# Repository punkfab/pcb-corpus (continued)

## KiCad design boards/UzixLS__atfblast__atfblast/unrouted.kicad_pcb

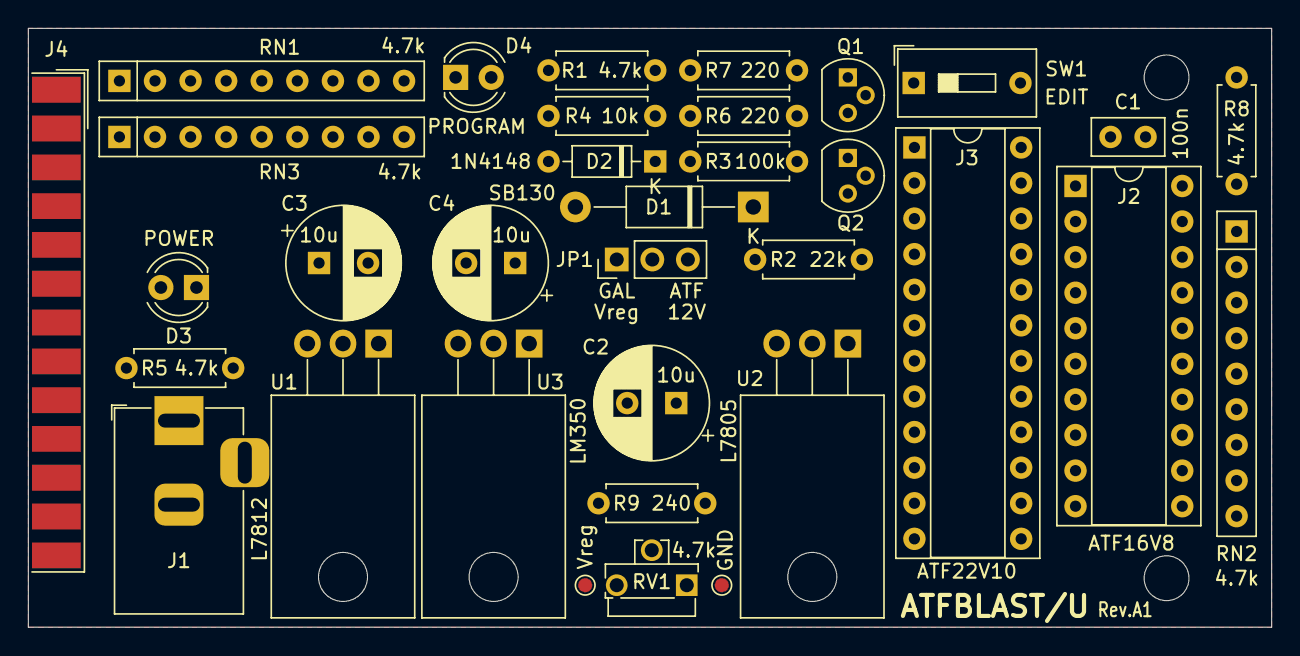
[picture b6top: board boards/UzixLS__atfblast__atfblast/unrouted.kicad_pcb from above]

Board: 2 copper layers, 88.8 x 42.8 mm, 36 parts (0 on the bottom side), 37 nets, no tracks yet.

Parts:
C1: 100n; C_Disc_D5.0mm_W2.5mm_P2.50mm
C2, C3, C4: 10u; CP_Radial_D8.0mm_P3.50mm
D1: SB130; D_DO-41_SOD81_P12.70mm_Horizontal
D2: 1N4148; D_DO-35_SOD27_P7.62mm_Horizontal
D3, D4: LED; LED_D4.0mm
H1, H2: MountingHole; MountingHole_3.2mm_M3
J1: DS-210; BarrelJack_Horizontal
J2: DIP20-panel; DIP-20_W7.62mm_Socket
J3: DIP24-panel; DIP-24_W7.62mm_Socket
J4: DB25_Male; DSUB-25_Male_EdgeMount_P2.77mm
JP1: Jumper_3; PinHeader_1x03_P2.54mm_Vertical
Q1: BC547; TO-92
Q2: BC557; TO-92
R1, R5, R8: 4.7k; R_Axial_DIN0207_L6.3mm_D2.5mm_P7.62mm_Horizontal
R2: 22k; R_Axial_DIN0207_L6.3mm_D2.5mm_P7.62mm_Horizontal
R3: 100k; R_Axial_DIN0207_L6.3mm_D2.5mm_P7.62mm_Horizontal
R4: 10k; R_Axial_DIN0207_L6.3mm_D2.5mm_P7.62mm_Horizontal
R6, R7: 220; R_Axial_DIN0207_L6.3mm_D2.5mm_P7.62mm_Horizontal
R9: 240; R_Axial_DIN0207_L6.3mm_D2.5mm_P7.62mm_Horizontal
RN1, RN2, RN3: 4.7k; R_Array_SIP9
RV1: 4.7k; Potentiometer_Runtron_RM-063_Horizontal
SW1: SW_DIP_x01; SW_DIP_SPSTx01_Slide_9.78x4.72mm_W7.62mm_P2.54mm
TP1: Vreg; TestPoint_Pad_D1.0mm
TP2: GND; TestPoint_Pad_D1.0mm
U1: L7812; TO-220-3_Horizontal_TabDown
U2: L7805; TO-220-3_Horizontal_TabDown
U3: LM350; TO-220-3_Horizontal_TabDown

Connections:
+5V: C1.1, C2.1, D2.2 (A), J2.20, J3.24, R5.1, RN1.1 (common), RN3.1 (common), U2.3 (OUT)
+12V: C3.1, D1.2 (A), JP1.3 (B), U1.3 (OUT), U2.1 (IN)
/ACK: J2.12, J3.14, J4.10, RN3.6 (R5)
/AUTO: J4.14, R4.2
/D0: J2.9, J3.11, J4.2, RN1.3 (R2)
/D1: J4.3, R6.2, RN1.4 (R3)
/D2: J2.3, J3.5, J4.4, RN1.5 (R4)
/D3: J2.4, J3.6, J4.5, RN1.7 (R6)
/D4: J2.5, J3.7, J4.6, RN3.2 (R1)
/D5: J2.6, J3.8, J4.7, RN3.3 (R2)
/D6: J2.7, J3.9, J4.8, RN3.4 (R3)
/D7: J2.8, J3.10, J4.9, RN3.5 (R4)
/EDIT: D2.1 (K), J2.2, J3.2, SW1.2
/P_V-: J2.19, J3.3, R7.1
/RA0: J2.18, J3.4, R6.1
/SELECT: J4.17, R7.2, RN1.6 (R5)
/STROBE: J2.11, J3.13, J4.1, RN1.2 (R1)
GND: C1.2, C2.2, C3.2, C4.2, D3.1 (K), J1.2, J1.3, J2.1, J2.10, J3.1, J3.12, J4.18, J4.19, J4.20, J4.21, J4.22, J4.23, J4.24, Q1.3 (E), R8.2, RN2.1 (common), RV1.2, TP2.1, U1.2 (GND), U2.2 (GND)
unnamed: C4.1, JP1.1 (A), R9.1, TP1.1, U3.2 (VO)
unnamed: D1.1 (K), Q2.3 (C), SW1.1
unnamed: D3.2 (A), R5.2
unnamed: D4.1 (K), Q1.1 (C), R3.1
unnamed: D4.2 (A), R1.2
unnamed: J1.1, U1.1 (IN), U3.3 (VI)
unnamed: J2.13, J3.15, RN2.9 (R8)
unnamed: J2.14, J3.16, RN2.8 (R7)
unnamed: J2.15, J3.17, RN2.7 (R6)
unnamed: J2.16, J3.18, RN2.6 (R5)
unnamed: J2.17, J3.19, RN2.5 (R4)
unnamed: J3.20, RN2.4 (R3)
unnamed: J3.21, RN2.3 (R2)
unnamed: J3.22, RN2.2 (R1)
unnamed: J3.23, R8.1
unnamed: JP1.2 (C), Q2.1 (E), R1.1, R2.2
unnamed: Q1.2 (B), R4.1
unnamed: Q2.2 (B), R2.1, R3.2
unnamed: R9.2, RV1.3, U3.1 (ADJ)

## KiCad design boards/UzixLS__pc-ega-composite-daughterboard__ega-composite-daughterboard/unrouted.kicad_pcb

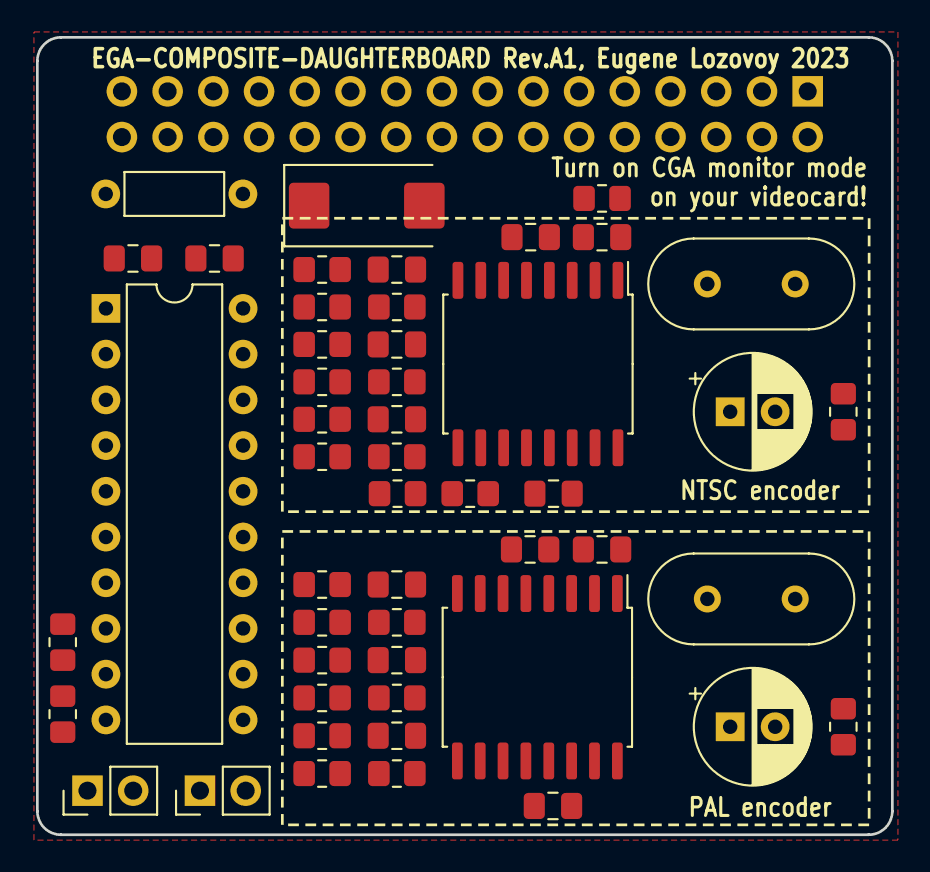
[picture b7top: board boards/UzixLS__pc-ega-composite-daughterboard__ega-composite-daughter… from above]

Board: 2 copper layers, 47.5 x 44.3 mm, 51 parts (1 on the bottom side), 43 nets, no tracks yet.

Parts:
C1, C2, C3, C6, C7, C8: 100n; C_0805_2012Metric_Pad1.18x1.45mm_HandSolder
C4, C9: 220u; CP_Radial_D6.3mm_P2.50mm
C5, C10: 4.3p; C_0805_2012Metric_Pad1.18x1.45mm_HandSolder
C11: 220u/10V; CP_EIA-7343-31_Kemet-D_Pad2.25x2.55mm_HandSolder
C12, C13, C14, C15, C16, C17: 1u; C_0805_2012Metric_Pad1.18x1.45mm_HandSolder
FB1: FB_Lossy; L_Axial_L5.3mm_D2.2mm_P7.62mm_Horizontal_Vishay_IM-1
J1: EGA Feature Connector; PinHeader_2x16_P2.54mm_Vertical
JP1, JP2: Jumper_2_Open; PinHeader_1x02_P2.54mm_Vertical
R1, R3, R5, R13, R15, R17: 390; R_0805_2012Metric_Pad1.20x1.40mm_HandSolder
R2, R4, R6, R14, R16, R18: 680; R_0805_2012Metric_Pad1.20x1.40mm_HandSolder
R7, R8, R9, R10, R19, R20, R21, R22: 75; R_0805_2012Metric_Pad1.20x1.40mm_HandSolder
R11, R12: 10k; R_0805_2012Metric_Pad1.20x1.40mm_HandSolder
R23, R24, R25: 0; R_0805_2012Metric_Pad1.20x1.40mm_HandSolder
U1, U3: AD724; SOIC-16W_7.5x10.3mm_P1.27mm
U2: ATF16V8; DIP-20_W7.62mm
Y1: 3.579545 MHz; Crystal_HC49-4H_Vertical
Y2: 4.433619 MHz; Crystal_HC49-4H_Vertical

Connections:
+5V: C13.2, FB1.1, J1.32
+5VA: C11.1, C12.2, C14.2, C15.2, C16.2, C17.2, FB1.2, R11.1, R12.1, R24.2, U1.1 (STDN), U1.4 (AVCC), U1.5 (ENCD), U1.14 (DVCC), U2.20 (VCC), U3.4 (AVCC), U3.5 (ENCD), U3.14 (DVCC)
/14M: J1.26, R23.2
/B0: R6.1, R18.1, U2.19 (IO1)
/B0_IN: J1.23, U2.6 (I6)
/B1: R5.1, R17.1, U2.18 (IO2)
/B1_IN: J1.14, U2.3 (I3)
/G0: R4.1, R16.1, U2.17 (I03)
/G0_IN: J1.22, U2.8 (I8)
/G1: R3.1, R15.1, U2.16 (IO4)
/G1_IN: J1.12, U2.4 (I4)
/HIN: J1.24, U2.7 (I7)
/HSYNC: U1.16 (HSYNC), U2.12 (IO8), U3.16 (HSYNC)
/NTSC: J1.4, R7.1
/PAL: J1.5, R19.1
/R0: R2.1, R14.1, U2.15 (IO5)
/R0_IN: J1.13, U2.2 (I2)
/R1: R1.1, R13.1, U2.14 (IO6)
/R1_IN: J1.15, U2.1 (I1/CLK)
/VIN: J1.25, U2.5 (I5)
/VSYNC: U1.15 (VSYNC), U2.13 (IO7), U3.15 (VSYNC)
GND: C5.2, C10.2, C11.2, C12.1, C13.1, C14.1, C15.1, C16.1, C17.1, J1.1, J1.31, JP1.2 (B), JP2.2 (B), R8.2, R9.2, R10.2, R20.2, R21.2, R22.2, R25.1, U1.2 (AGND), U1.13 (DGND), U2.10 (GND), U3.1 (STDN), U3.2 (AGND), U3.12 (SELECT), U3.13 (DGND), Y1.2, Y2.2
unnamed: C1.2, R1.2, R2.2, R8.1
unnamed: C2.2, R3.2, R4.2, R9.1
unnamed: C3.2, R5.2, R6.2, R10.1
unnamed: C4.2, R7.2
unnamed: C6.2, R13.2, R14.2, R20.1
unnamed: C7.2, R15.2, R16.2, R21.1
unnamed: C8.2, R17.2, R18.2, R22.1
unnamed: C9.2, R19.2
unnamed: JP1.1 (A), R11.2, U2.9 (I9)
unnamed: JP2.1 (A), R12.2, U2.11 (I10/~OE)
unnamed: C3.1, U1.8 (BIN)
unnamed: C4.1, U1.10 (COMP)
unnamed: C5.1, R23.1, U1.3 (FIN), Y1.1
unnamed: C2.1, U1.7 (GIN)
unnamed: C1.1, U1.6 (RIN)
unnamed: R24.1, R25.2, U1.12 (SELECT)
unnamed: C8.1, U3.8 (BIN)
unnamed: C9.1, U3.10 (COMP)
unnamed: C10.1, U3.3 (FIN), Y2.1
unnamed: C7.1, U3.7 (GIN)
unnamed: C6.1, U3.6 (RIN)
